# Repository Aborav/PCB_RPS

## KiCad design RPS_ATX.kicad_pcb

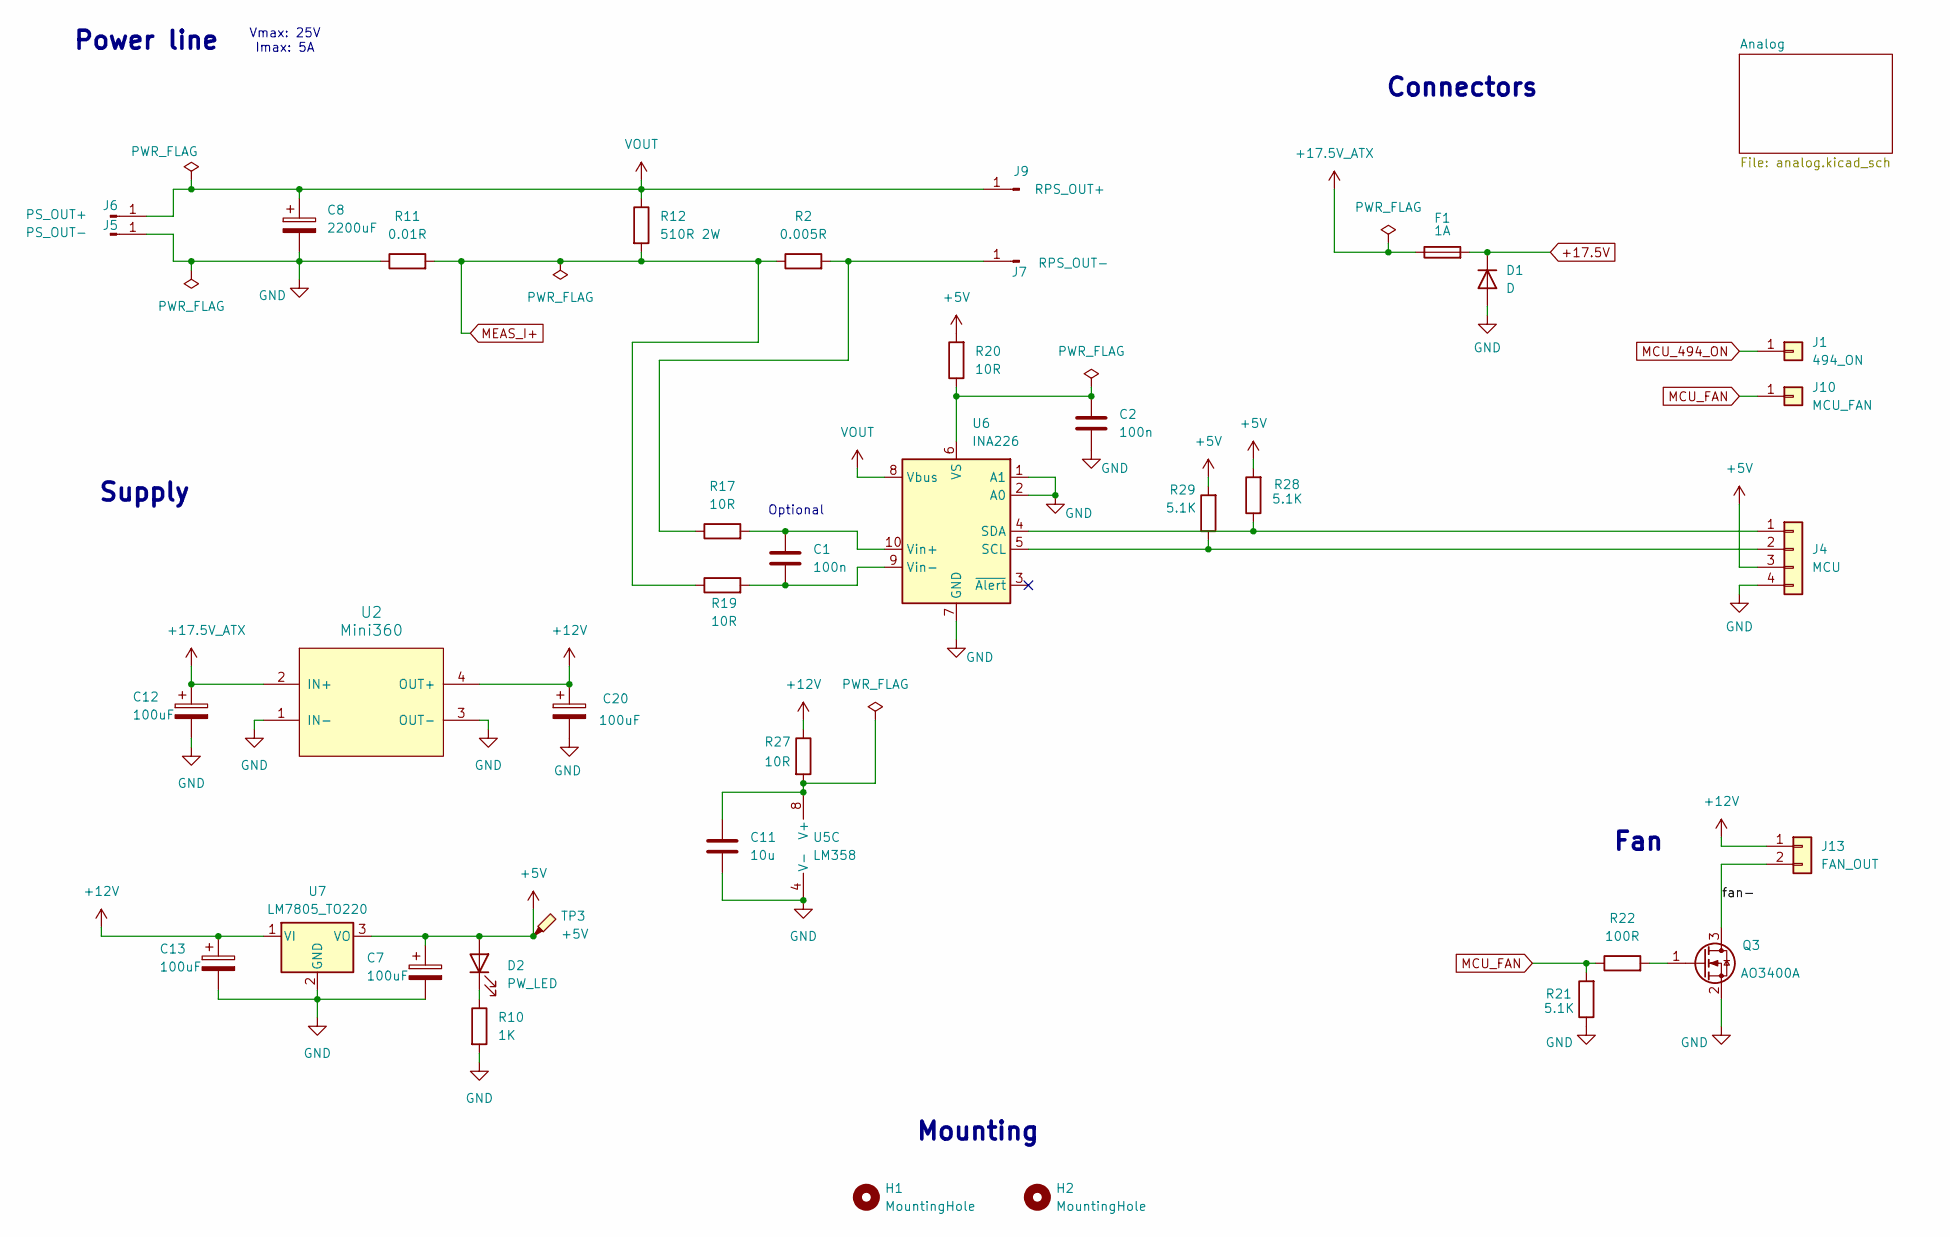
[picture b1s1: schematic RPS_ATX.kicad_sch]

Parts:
C1, C2: 100n; C_0805_2012Metric_Pad1.18x1.45mm_HandSolder
C7, C12, C13, C20: 100uF; CP_Elec_6.3x5.4_Nichicon
C8: 2200uF; CP_Radial_D18.0mm_P7.50mm
C11: 10u; C_1206_3216Metric_Pad1.33x1.80mm_HandSolder
D1: D; D_1206_3216Metric_Pad1.42x1.75mm_HandSolder
D2: PW_LED; LED_1206_3216Metric_Pad1.42x1.75mm_HandSolder
F1: 1A; Fuse_1206_3216Metric_Pad1.42x1.75mm_HandSolder
H1, H2: MountingHole; MountingHole_4.3mm_M4
J1: 494_ON; PinHeader_1x01_P2.54mm_Vertical
J4: MCU; PinHeader_1x04_P2.54mm_Vertical
J5: PS_OUT-; SolderWire-2sqmm_1x01_D2mm_OD3.9mm
J6: PS_OUT+; SolderWire-2sqmm_1x01_D2mm_OD3.9mm
J7: RPS_OUT-; SolderWire-2sqmm_1x01_D2mm_OD3.9mm
J9: RPS_OUT+; SolderWire-2sqmm_1x01_D2mm_OD3.9mm
J10: MCU_FAN; PinHeader_1x01_P2.54mm_Vertical
J13: FAN_OUT; PinHeader_1x02_P2.54mm_Vertical
Q3: AO3400A; SOT-23
R2: 0.005R; Shunt 0.005R
R10: 1K; R_1206_3216Metric_Pad1.30x1.75mm_HandSolder
R11: 0.01R; Resistor_Shunt_L10_D3.7
R12: 510R 2W; R_Axial_Power_L25.0mm_W9.0mm_P7.62mm_Vertical
R17, R19, R20, R27: 10R; R_1206_3216Metric_Pad1.30x1.75mm_HandSolder
R21, R28, R29: 5.1K; R_0805_2012Metric_Pad1.20x1.40mm_HandSolder
R22: 100R; R_1206_3216Metric_Pad1.30x1.75mm_HandSolder
TP3: +5V; TestPoint_Pad_D2.0mm
U2: Mini360; Mini360_step-down
U5: LM358; SOIC-8_3.9x4.9mm_P1.27mm
U6: INA226; VSSOP-10_3x3mm_P0.5mm
U7: LM7805_TO220; TO-220-3_Vertical

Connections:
+5V: C7.1, D2.2 (A), J4.3, R20.2, R28.2, R29.2, TP3.1, U7.3 (VO)
+12V: C13.1, C20.1, J13.1, R27.1, U2.4 (OUT+), U7.1 (VI)
+17.5V: D1.1 (K), F1.2; also elsewhere on the board
+17.5V_ATX: C12.1, F1.1, U2.2 (IN+); also elsewhere on the board
/fan-: J13.2, Q3.3 (D)
GND: C2.2, C7.2, C8.2, C11.2, C12.2, C13.2, C20.2, D1.2 (A), J4.4, J5.1, Q3.2 (S), R10.2, R11.1, R21.1, U2.1 (IN-), U2.3 (OUT-), U5.4 (V-), U6.1 (A1), U6.2 (A0), U6.7 (GND), U7.2 (GND); also elsewhere on the board
MCU_494_ON: J1.1; also elsewhere on the board
MCU_FAN: J10.1, R21.2, R22.1
MEAS_I+: R2.1, R11.2, R12.2, R19.1; also elsewhere on the board
unnamed: D2.1 (K), R10.1
unnamed: J4.1, R28.1, U6.4 (SDA)
unnamed: J4.2, R29.1, U6.5 (SCL)
unnamed: J7.1, R2.2, R17.1
unnamed: Q3.1 (G), R22.2
unnamed: C11.1, R27.2, U5.8 (V+)
unnamed: C2.1, R20.1, U6.6 (VS)
unnamed: C1.1, R17.2, U6.10 (Vin+)
unnamed: C1.2, R19.2, U6.9 (Vin-)
VOUT: C8.1, J6.1, J9.1, R12.1, U6.8 (Vbus); also elsewhere on the board

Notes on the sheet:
Power line
Optional
Supply
Vmax: 25V Imax: 5A
Fan
Mounting
Connectors

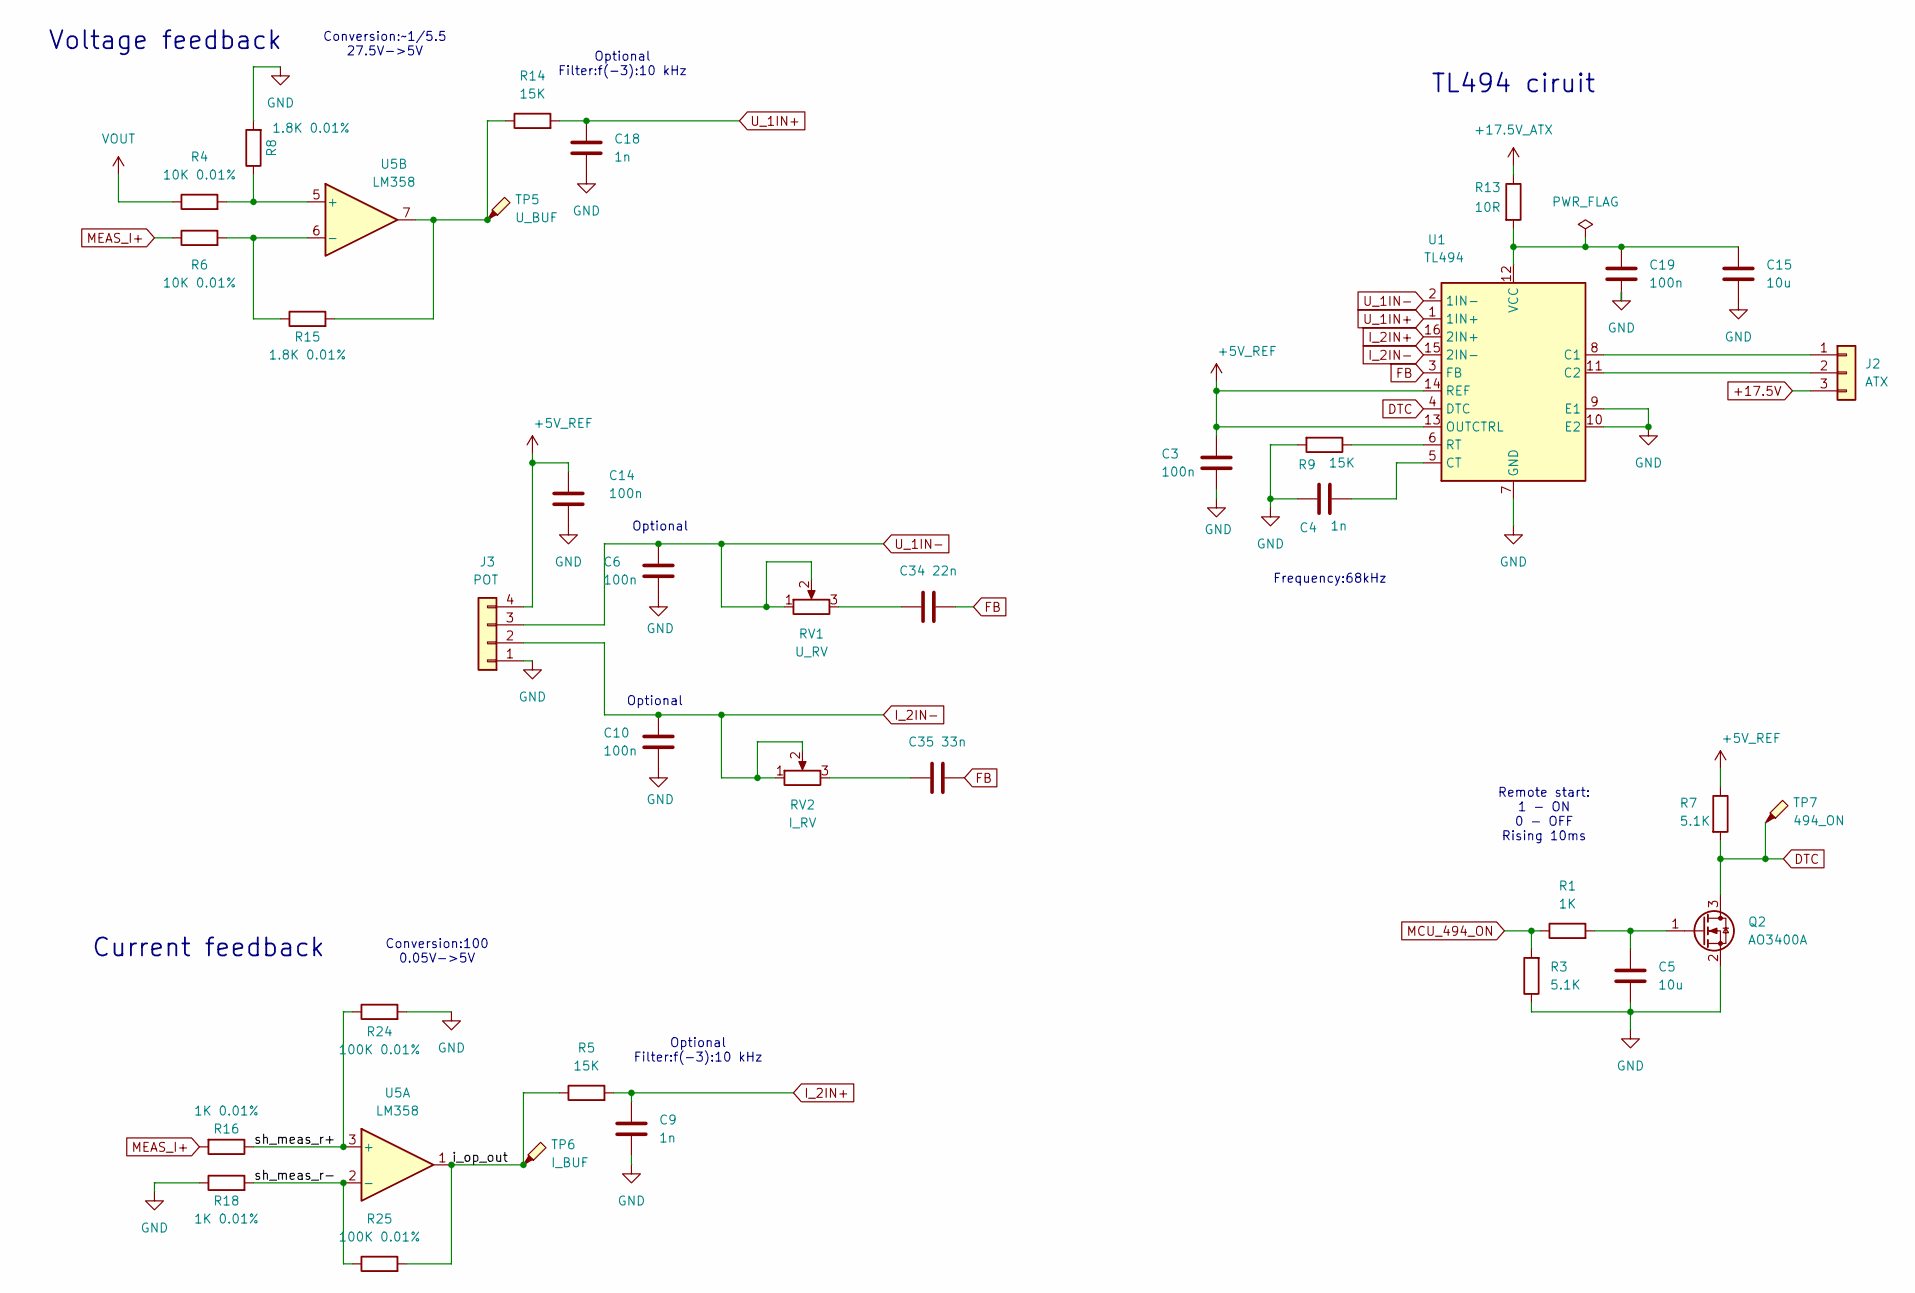
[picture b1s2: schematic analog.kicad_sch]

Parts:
C3, C6, C10, C14, C19: 100n; C_0805_2012Metric_Pad1.18x1.45mm_HandSolder
C4, C9, C18: 1n; C_1206_3216Metric_Pad1.33x1.80mm_HandSolder
C5, C15: 10u; C_1206_3216Metric_Pad1.33x1.80mm_HandSolder
C34: 22n; C_1206_3216Metric_Pad1.33x1.80mm_HandSolder
C35: 33n; C_1206_3216Metric_Pad1.33x1.80mm_HandSolder
J2: ATX; PinHeader_1x03_P2.54mm_Vertical
J3: POT; PinHeader_1x04_P2.54mm_Vertical
Q2: AO3400A; SOT-23
R1: 1K; R_1206_3216Metric_Pad1.30x1.75mm_HandSolder
R3, R7: 5.1K; R_0805_2012Metric_Pad1.20x1.40mm_HandSolder
R4, R6: 10K 0.01%; R_0805_2012Metric_Pad1.20x1.40mm_HandSolder
R5, R9, R14: 15K; R_1206_3216Metric_Pad1.30x1.75mm_HandSolder
R8, R15: 1.8K 0.01%; R_0805_2012Metric_Pad1.20x1.40mm_HandSolder
R13: 10R; R_1206_3216Metric_Pad1.30x1.75mm_HandSolder
R16, R18: 1K 0.01%; R_0805_2012Metric_Pad1.20x1.40mm_HandSolder
R24, R25: 100K 0.01%; R_1206_3216Metric_Pad1.30x1.75mm_HandSolder
RV1: U_RV; Potentiometer_Bourns_3299W_Vertical
RV2: I_RV; Potentiometer_Bourns_3299W_Vertical
TP5: U_BUF; TestPoint_Pad_D2.0mm
TP6: I_BUF; TestPoint_Pad_D2.0mm
TP7: 494_ON; TestPoint_Pad_D2.0mm
U1: TL494; SOIC-16_3.9x9.9mm_P1.27mm
U5: LM358; SOIC-8_3.9x4.9mm_P1.27mm

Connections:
+5V_REF: C3.1, C14.1, J3.4, R7.1, U1.13 (OUTCTRL), U1.14 (REF)
+17.5V: J2.3; also elsewhere on the board
+17.5V_ATX: R13.1; also elsewhere on the board
/Analog/i_op_out: R5.1, R25.2, TP6.1, U5.1
/Analog/sh_meas_r+: R16.1, R24.1, U5.3 (+)
/Analog/sh_meas_r-: R18.2, R25.1, U5.2 (-)
DTC: Q2.3 (D), R7.2, TP7.1, U1.4 (DTC)
FB: C34.2, C35.2, U1.3 (FB)
GND: C3.2, C4.1, C5.2, C6.2, C9.2, C10.2, C14.2, C15.2, C18.2, C19.2, J3.1, Q2.2 (S), R3.1, R8.2, R9.2, R18.1, R24.2, U1.7 (GND), U1.9 (E1), U1.10 (E2); also elsewhere on the board
I_2IN+: C9.1, R5.2, U1.16 (2IN+)
I_2IN-: C10.1, J3.2, RV2.1, RV2.2, U1.15 (2IN-)
MCU_494_ON: R1.1, R3.2; also elsewhere on the board
MEAS_I+: R6.1, R16.2; also elsewhere on the board
unnamed: C34.1, RV1.3
unnamed: C35.1, RV2.3
unnamed: J2.1, U1.8 (C1)
unnamed: J2.2, U1.11 (C2)
unnamed: C5.1, Q2.1 (G), R1.2
unnamed: R14.1, R15.2, TP5.1, U5.7
unnamed: C4.2, U1.5 (CT)
unnamed: R9.1, U1.6 (RT)
unnamed: C15.1, C19.1, R13.2, U1.12 (VCC)
unnamed: R4.2, R8.1, U5.5 (+)
unnamed: R6.2, R15.1, U5.6 (-)
U_1IN+: C18.1, R14.2, U1.1 (1IN+)
U_1IN-: C6.1, J3.3, RV1.1, RV1.2, U1.2 (1IN-)
VOUT: R4.1; also elsewhere on the board

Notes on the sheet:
Current feedback
Frequency:68kHz
Optional Filter:f(-3):10 kHz
Optional
Remote start: 1 - ON 0 - OFF Rising 10ms
Conversion:~1/5.5 27.5V->5V
Conversion:100 0.05V->5V
Voltage feedback
TL494 ciruit

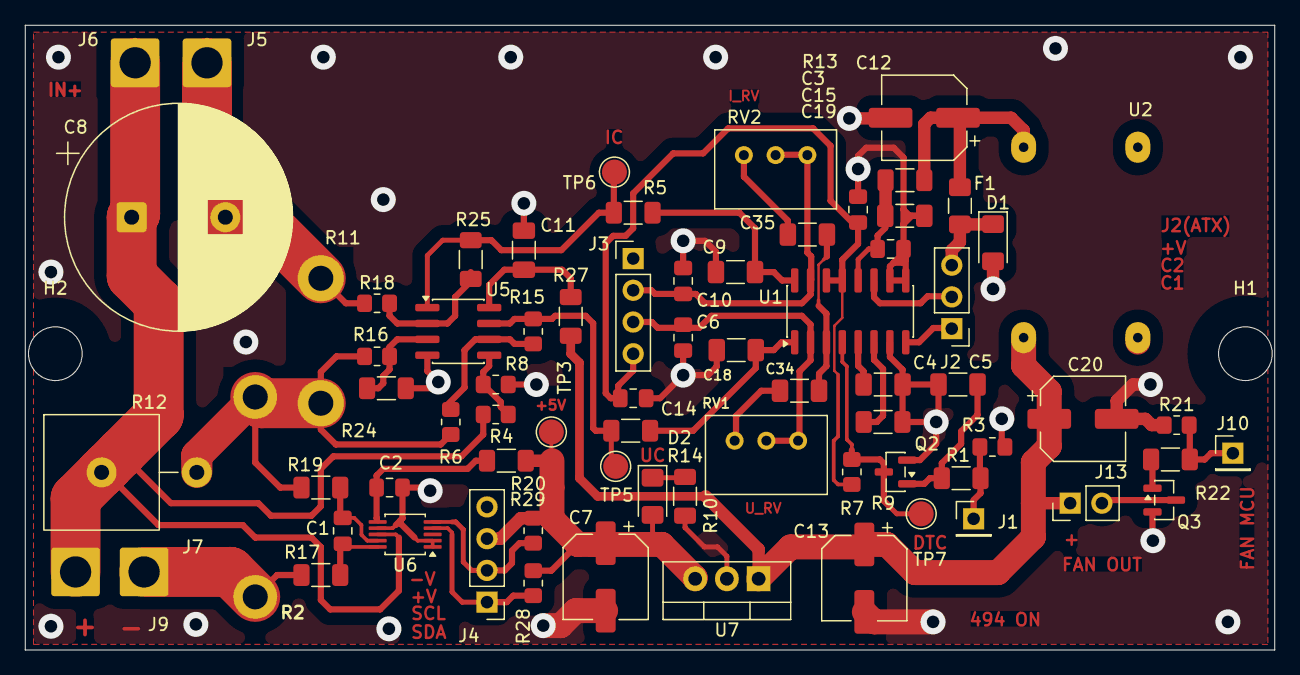
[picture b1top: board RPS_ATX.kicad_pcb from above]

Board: 2 copper layers, 100.0 x 50.0 mm, 75 parts (0 on the bottom side), 40 nets.

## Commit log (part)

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2026-03-17 project start. copy elements from TL494_DAC
2026-03-19 added: RC calculation,connectors Vin/Vmeas
2026-03-22 new OpAmp, new RC calc, G431 added
2026-03-23 MCU analog perephery, TL494 FB wiring
2026-03-24 assign footprints
2026-03-25 approximate location of the components at the PCB
2026-03-26 final location of the power,analog sections
2026-03-27 power/analog lines are finished
2026-04-30 added display and encoders signal lines, hints
2026-05-04 added fan control and ds18b20 to the schematic
2026-05-06 fan and temp sensor tracing
2026-05-08 minor changes (0805 for 0.1% R, new Y)
2026-05-08 rest of files
2026-06-21 changing concept
2026-06-26 excluding STM32G431
2026-06-27 lm358 as U and I meas
2026-06-28 added gnd vias, need to isolate power and signal GND
2026-06-28 kind of ready
